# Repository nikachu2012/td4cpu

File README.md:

# TD4 CPU
書籍「CPUの創りかた」にあるTD4 CPUの回路を、ユニバーサル基板で作るのがめんどくさかったので基板にしたものです。
製作の際は書籍を購入することをお勧めします。

*完成させた基板のサンプル*

## フォルダ解説
### `schematic`
回路図と基板のKiCadデータが入っています。バージョンは8.0です。
なんかのフットプリントをライブラリで入れてた気がしますがなくても読めるっぽいです。

### `schematic_pdf`
回路図のpdfファイルが入っています。

### `rom_emulator`
ArduinoなどのマイコンでROMを作るためのプログラムが入っています。  
Arduino UNO系と、Raspberry Pi Pico(MicroPython)があります。

#### Arduino UNO系
Arduino UNO R4 WiFiで動作確認しています。  
ポートレジスタの操作ではなく`digitalWrite`を使っているのでMinimaやR3でも動くと思います。

以下のように接続してください。

| Arduino側 | TD4 CPU側     |
| --------- | ------------- |
| VIN       | +5V           |
| GND       | GND           |
| D11       | Address bus 3 |
| D10       | Address bus 2 |
| D9        | Address bus 1 |
| D8        | Address bus 0 |
| D7        | Data bus 7    |
| D6        | Data bus 6    |
| D5        | Data bus 5    |
| D4        | Data bus 4    |
| D3        | Data bus 3    |
| D2        | Data bus 2    |
| D1        | Data bus 1    |
| D0        | Data bus 0    |

#### Raspberry Pi Pico
Raspberry Pi Pico無印で動作確認済みです。
ファイル名を`main.py`に変更して送信すれば動作すると思います。

以下のように接続してください。

| Raspberry Pi Pico側 | TD4 CPU側     |
| ------------------- | ------------- |
| 39 VSYS             | +5V           |
| 38 GND              | GND           |
| 4  GP2              | Address bus 3 |
| 5  GP3              | Address bus 2 |
| 6  GP4              | Address bus 1 |
| 7  GP5              | Address bus 0 |
| 9  GP6              | Data bus 7    |
| 10 GP7              | Data bus 6    |
| 11 GP8              | Data bus 5    |
| 12 GP9              | Data bus 4    |
| 13 GP10             | Data bus 3    |
| 14 GP11             | Data bus 2    |
| 15 GP12             | Data bus 1    |
| 16 GP13             | Data bus 0    |

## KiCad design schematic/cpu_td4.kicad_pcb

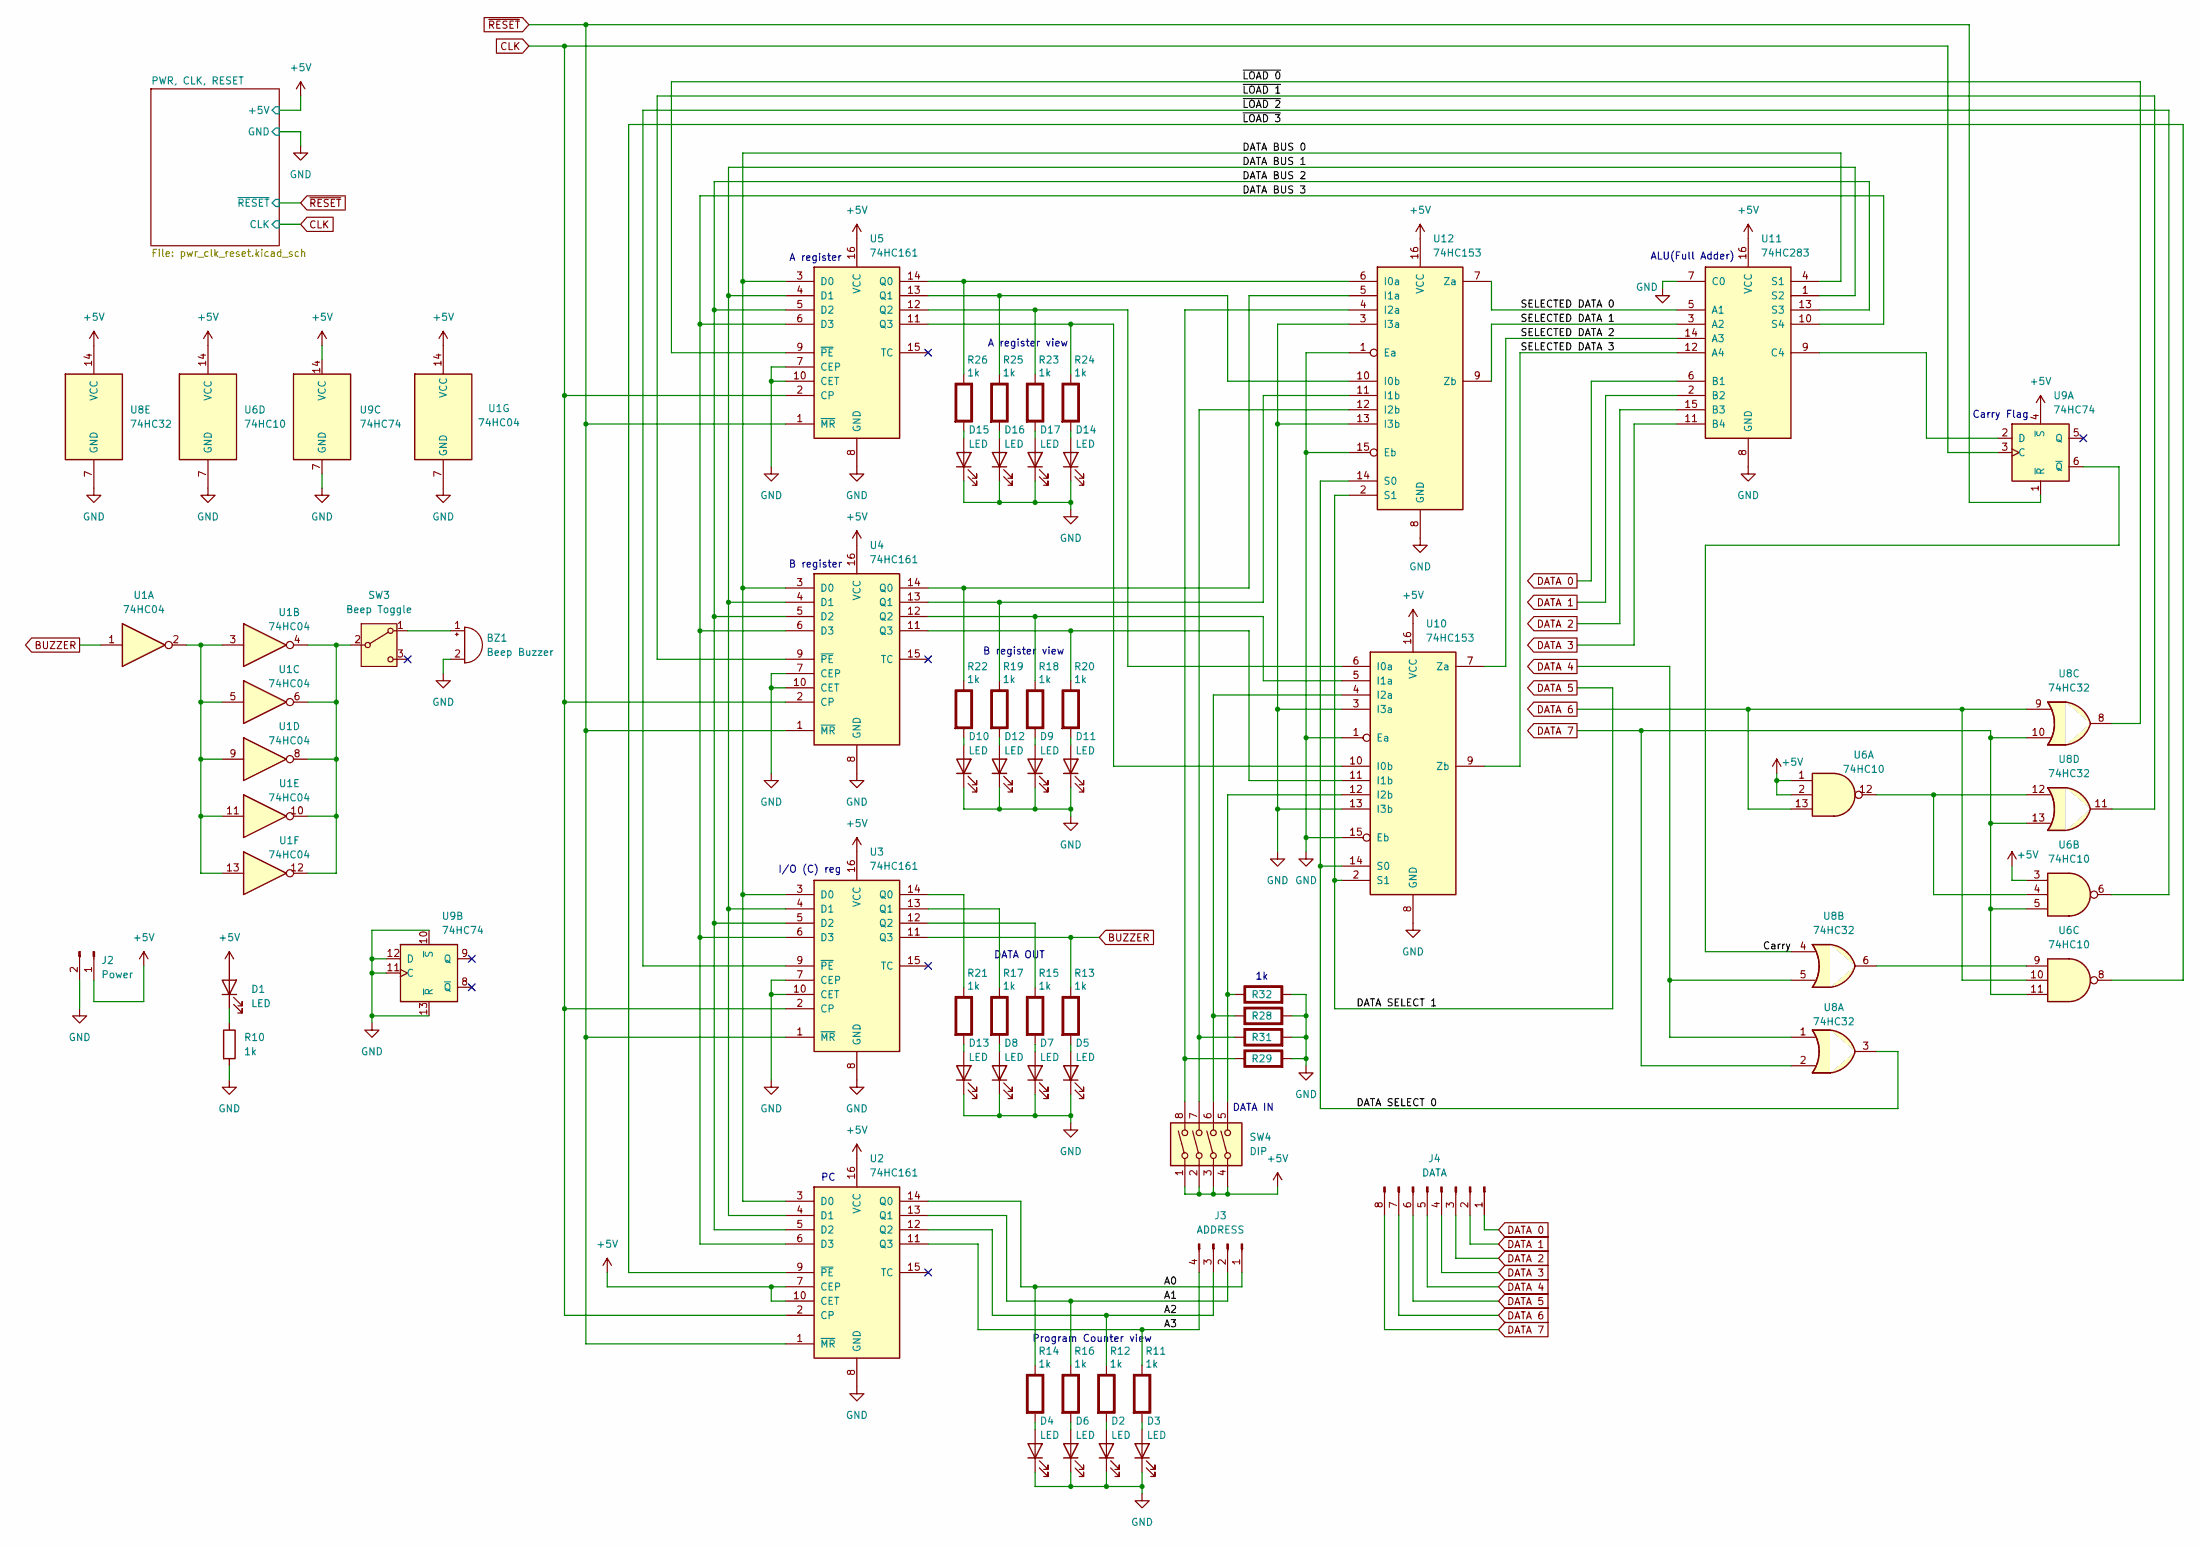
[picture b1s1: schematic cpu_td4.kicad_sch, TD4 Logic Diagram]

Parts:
BZ1: Beep Buzzer; Buzzer_12x9.5RM7.6
D1, D2, D3, D4, D5, D6, D7, D8, D9, D10, D11, D12, D13, D14, D15, D16, D17: LED; LED_D3.0mm
J2: Power; PinHeader_1x02_P2.54mm_Vertical
J3: ADDRESS; PinHeader_1x04_P2.54mm_Vertical
J4: DATA; PinHeader_1x08_P2.54mm_Vertical
R10: 1k; R_Axial_DIN0207_L6.3mm_D2.5mm_P7.62mm_Horizontal
R11, R12, R13, R14, R15, R16, R17, R18, R19, R20, R21, R22, R23, R24, R25, R26, R28, R29, R31, R32: 1k; R_Axial_DIN0207_L6.3mm_D2.5mm_P7.62mm_Horizontal; Rating W
SW3: Beep Toggle; SS12D00G3
SW4: DIP; SW_DIP_SPSTx04_Slide_9.78x12.34mm_W7.62mm_P2.54mm
U1: 74HC04; DIP-14_W7.62mm_Socket
U2, U3, U4, U5: 74HC161; DIP-16_W7.62mm_Socket
U6: 74HC10; DIP-14_W7.62mm_Socket
U8: 74HC32; DIP-14_W7.62mm_Socket
U9: 74HC74; DIP-14_W7.62mm_Socket
U10, U12: 74HC153; DIP-16_W7.62mm_Socket
U11: 74HC283; DIP-16_W7.62mm_Socket

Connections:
+5V: D1.2 (A), J2.1, SW4.1, SW4.2, SW4.3, SW4.4, U1.14 (VCC), U2.7 (CEP), U2.10 (CET), U2.16 (VCC), U3.16 (VCC), U4.16 (VCC), U5.16 (VCC), U6.1, U6.2, U6.3, U6.14 (VCC), U8.14 (VCC), U9.4 (~S), U9.14 (VCC), U10.16 (VCC), U11.16 (VCC), U12.16 (VCC); also elsewhere on the board
/A0: J3.1, R14.1 (+), U2.14 (Q0)
/A1: J3.2, R16.1 (+), U2.13 (Q1)
/A2: J3.3, R12.1 (+), U2.12 (Q2)
/A3: J3.4, R11.1 (+), U2.11 (Q3)
/Carry: U8.4, U9.6 (~Q)
/DATA BUS 0: U2.3 (D0), U3.3 (D0), U4.3 (D0), U5.3 (D0), U11.4 (S1)
/DATA BUS 1: U2.4 (D1), U3.4 (D1), U4.4 (D1), U5.4 (D1), U11.1 (S2)
/DATA BUS 2: U2.5 (D2), U3.5 (D2), U4.5 (D2), U5.5 (D2), U11.13 (S3)
/DATA BUS 3: U2.6 (D3), U3.6 (D3), U4.6 (D3), U5.6 (D3), U11.10 (S4)
/DATA SELECT 0: U8.3, U10.14 (S0), U12.14 (S0)
/SELECTED DATA 0: U11.5 (A1), U12.7 (Za)
/SELECTED DATA 1: U11.3 (A2), U12.9 (Zb)
/SELECTED DATA 2: U10.7 (Za), U11.14 (A3)
/SELECTED DATA 3: U10.9 (Zb), U11.12 (A4)
/~LOAD 0: U5.9 (~PE), U8.8
/~LOAD 1: U4.9 (~PE), U8.11
/~LOAD 2: U3.9 (~PE), U6.6
/~LOAD 3: U2.9 (~PE), U6.8
BUZZER: R13.1 (+), U1.1, U3.11 (Q3)
CLK: U2.2 (CP), U3.2 (CP), U4.2 (CP), U5.2 (CP), U9.3 (C); also elsewhere on the board
DATA 0: J4.1, U11.6 (B1)
DATA 1: J4.2, U11.2 (B2)
DATA 2: J4.3, U11.15 (B3)
DATA 3: J4.4, U11.11 (B4)
DATA 4: J4.5, U8.1, U8.5
DATA 5: J4.6, U10.2 (S1), U12.2 (S1)
DATA 6: J4.7, U6.10, U6.13, U8.9
DATA 7: J4.8, U6.5, U6.11, U8.2, U8.10, U8.13
GND: BZ1.2 (-), D2.1 (K), D3.1 (K), D4.1 (K), D5.1 (K), D6.1 (K), D7.1 (K), D8.1 (K), D9.1 (K), D10.1 (K), D11.1 (K), D12.1 (K), D13.1 (K), D14.1 (K), D15.1 (K), D16.1 (K), D17.1 (K), J2.2, R10.2, R28.2 (-), R29.2 (-), R31.2 (-), R32.2 (-), U1.7 (GND), U2.8 (GND), U3.7 (CEP), U3.8 (GND), U3.10 (CET), U4.7 (CEP), U4.8 (GND), U4.10 (CET), U5.7 (CEP), U5.8 (GND), U5.10 (CET), U6.7 (GND), U8.7 (GND), U9.7 (GND), U9.10 (~S), U9.11 (C), U9.12 (D), U9.13 (~R), U10.1 (Ea), U10.3 (I3a), U10.8 (GND), U10.13 (I3b), U10.15 (Eb), U11.7 (C0), U11.8 (GND), U12.1 (Ea), U12.3 (I3a), U12.8 (GND), U12.13 (I3b), U12.15 (Eb); also elsewhere on the board
unnamed: BZ1.1 (+), SW3.1 (A)
unnamed: D1.1 (K), R10.1
unnamed: D2.2 (A), R12.2 (-)
unnamed: D3.2 (A), R11.2 (-)
unnamed: D4.2 (A), R14.2 (-)
unnamed: D5.2 (A), R13.2 (-)
unnamed: D6.2 (A), R16.2 (-)
unnamed: D7.2 (A), R15.2 (-)
unnamed: D8.2 (A), R17.2 (-)
unnamed: D9.2 (A), R18.2 (-)
unnamed: D10.2 (A), R22.2 (-)
unnamed: D11.2 (A), R20.2 (-)
unnamed: D12.2 (A), R19.2 (-)
unnamed: D13.2 (A), R21.2 (-)
unnamed: D14.2 (A), R24.2 (-)
unnamed: D15.2 (A), R26.2 (-)
unnamed: D16.2 (A), R25.2 (-)
unnamed: D17.2 (A), R23.2 (-)
unnamed: R15.1 (+), U3.12 (Q2)
unnamed: R17.1 (+), U3.13 (Q1)
unnamed: R18.1 (+), U4.12 (Q2), U10.5 (I1a)
unnamed: R19.1 (+), U4.13 (Q1), U12.11 (I1b)
unnamed: R20.1 (+), U4.11 (Q3), U10.11 (I1b)
unnamed: R21.1 (+), U3.14 (Q0)
unnamed: R22.1 (+), U4.14 (Q0), U12.5 (I1a)
unnamed: R23.1 (+), U5.12 (Q2), U10.6 (I0a)
unnamed: R24.1 (+), U5.11 (Q3), U10.10 (I0b)
unnamed: R25.1 (+), U5.13 (Q1), U12.10 (I0b)
unnamed: R26.1 (+), U5.14 (Q0), U12.6 (I0a)
unnamed: R28.1 (+), SW4.6, U10.4 (I2a)
unnamed: R29.1 (+), SW4.8, U12.4 (I2a)
unnamed: R31.1 (+), SW4.7, U12.12 (I2b)
unnamed: R32.1 (+), SW4.5, U10.12 (I2b)
unnamed: SW3.2 (B), U1.4, U1.6, U1.8, U1.10, U1.12
unnamed: U1.2, U1.3, U1.5, U1.9, U1.11, U1.13
unnamed: U6.9, U8.6
unnamed: U6.4, U6.12, U8.12
unnamed: U9.2 (D), U11.9 (C4)
~RESET: U2.1 (~MR), U3.1 (~MR), U4.1 (~MR), U5.1 (~MR), U9.1 (~R); also elsewhere on the board

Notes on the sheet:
ALU(Full Adder)
A register view
DATA OUT
B register
I/O (C) reg
Program Counter view
B register view
A register
DATA IN
Carry Flag

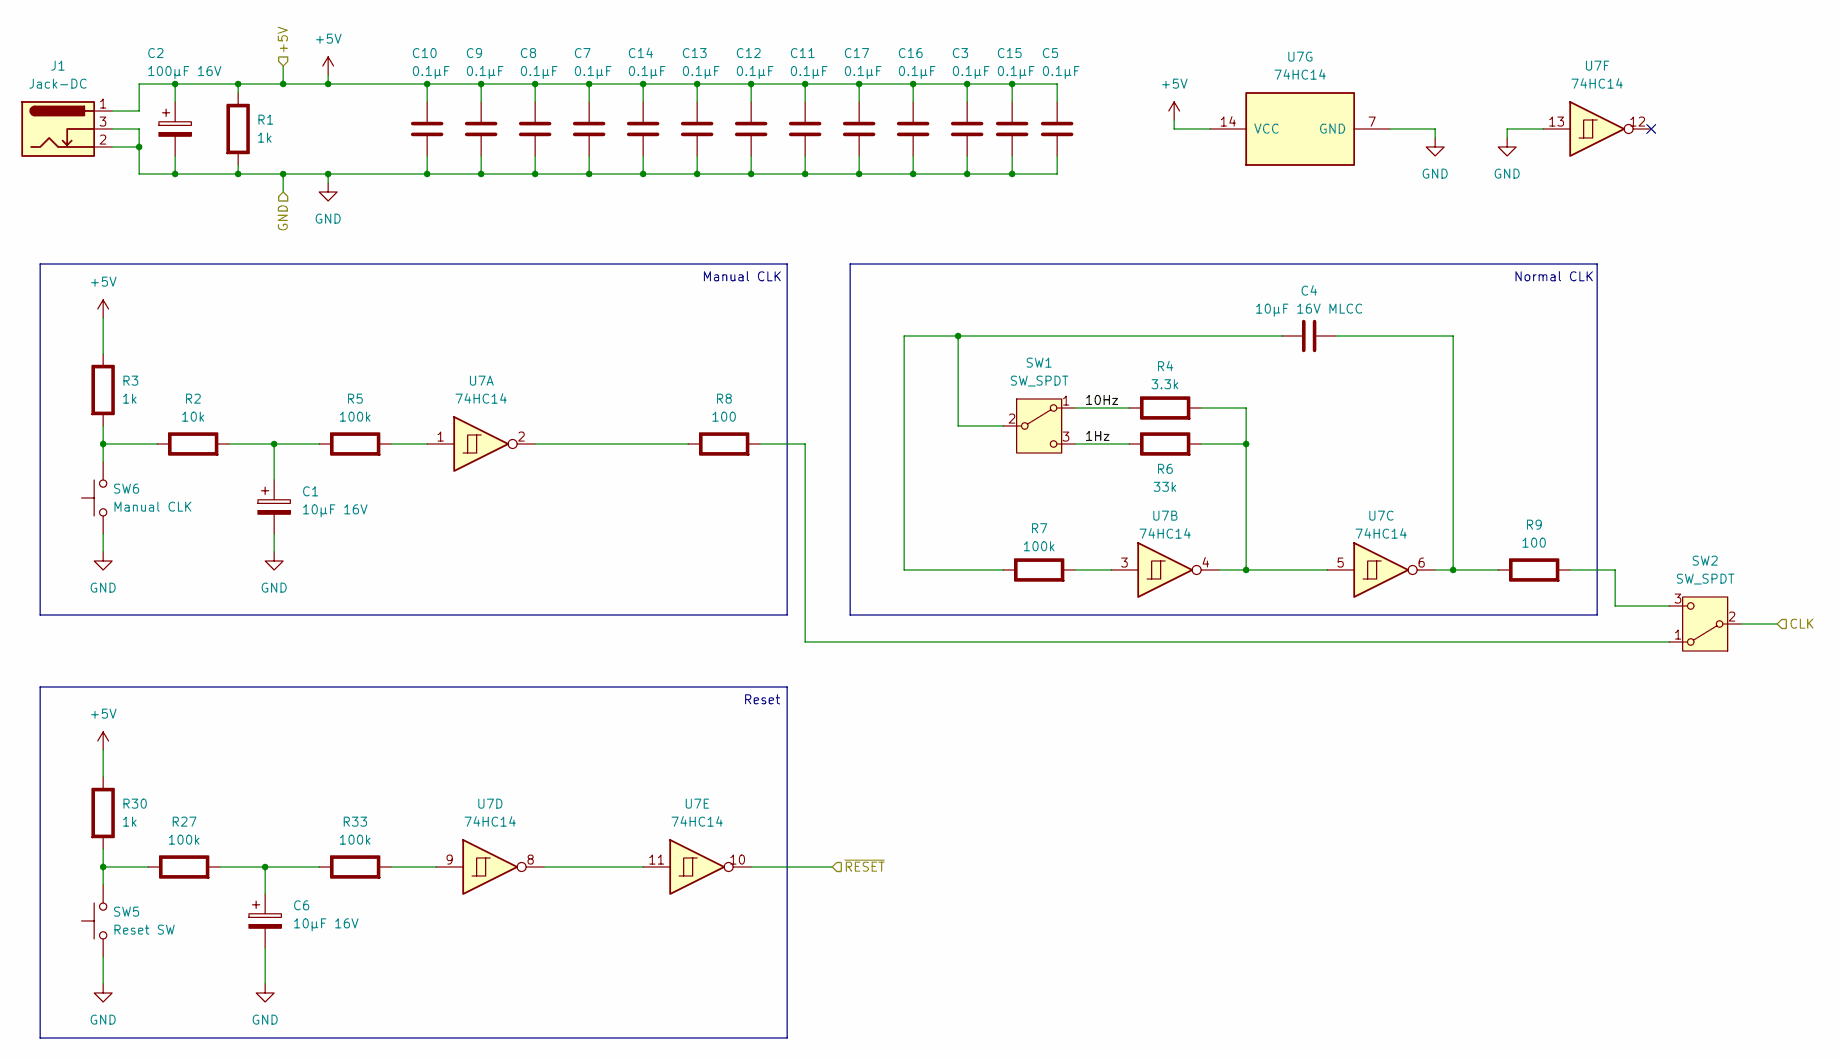
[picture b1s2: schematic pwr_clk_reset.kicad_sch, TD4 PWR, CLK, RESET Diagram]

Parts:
C1, C6: 10μF 16V; CP_Radial_D4.0mm_P1.50mm
C2: 100μF 16V; CP_Radial_D6.3mm_P2.50mm
C3, C5, C7, C8, C9, C10, C11, C12, C13, C14, C15, C16, C17: 0.1μF; C_Disc_D5.0mm_W2.5mm_P2.50mm
C4: 10μF 16V MLCC; C_Disc_D6.0mm_W2.5mm_P5.00mm
J1: Jack-DC; BarrelJack_GCT_DCJ200-10-A_Horizontal
R1, R3, R30: 1k; R_Axial_DIN0207_L6.3mm_D2.5mm_P7.62mm_Horizontal; Rating W
R2: 10k; R_Axial_DIN0207_L6.3mm_D2.5mm_P7.62mm_Horizontal; Rating W
R4: 3.3k; R_Axial_DIN0207_L6.3mm_D2.5mm_P7.62mm_Horizontal; Rating W
R5, R7, R27, R33: 100k; R_Axial_DIN0207_L6.3mm_D2.5mm_P7.62mm_Horizontal; Rating W
R6: 33k; R_Axial_DIN0207_L6.3mm_D2.5mm_P7.62mm_Horizontal; Rating W
R8, R9: 100; R_Axial_DIN0207_L6.3mm_D2.5mm_P7.62mm_Horizontal; Rating W
SW1, SW2: SW_SPDT; SS12D00G3
SW5: Reset SW; SW_PUSH-12mm_Wuerth-430476085716
SW6: Manual CLK; SW_PUSH-12mm_Wuerth-430476085716
U7: 74HC14; DIP-14_W7.62mm_Socket

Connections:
+5V: C2.1, C3.1, C5.1, C7.1, C8.1, C9.1, C10.1, C11.1, C12.1, C13.1, C14.1, C15.1, C16.1, C17.1, J1.1, R1.1 (+), R3.1 (+), R30.1 (+), U7.14 (VCC); also elsewhere on the board
/PWR, CLK, RESET/1Hz: R6.1 (+), SW1.3 (C)
/PWR, CLK, RESET/10Hz: R4.1 (+), SW1.1 (A)
CLK: SW2.2 (B); also elsewhere on the board
GND: C1.2, C2.2, C3.2, C5.2, C6.2, C7.2, C8.2, C9.2, C10.2, C11.2, C12.2, C13.2, C14.2, C15.2, C16.2, C17.2, J1.2, J1.3, R1.2 (-), SW5.1, SW6.1, U7.7 (GND), U7.13; also elsewhere on the board
unnamed: R2.1 (+), R3.2 (-), SW6.2
unnamed: C1.1, R2.2 (-), R5.1 (+)
unnamed: R4.2 (-), R6.2 (-), U7.4, U7.5
unnamed: R5.2 (-), U7.1
unnamed: C4.1, R7.1 (+), SW1.2 (B)
unnamed: R7.2 (-), U7.3
unnamed: R8.1 (+), U7.2
unnamed: R8.2 (-), SW2.1 (A)
unnamed: C4.2, R9.1 (+), U7.6
unnamed: R9.2 (-), SW2.3 (C)
unnamed: R27.1 (+), R30.2 (-), SW5.2
unnamed: C6.1, R27.2 (-), R33.1 (+)
unnamed: R33.2 (-), U7.9
unnamed: U7.8, U7.11
~RESET: U7.10; also elsewhere on the board

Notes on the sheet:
Manual CLK
Normal CLK
Reset

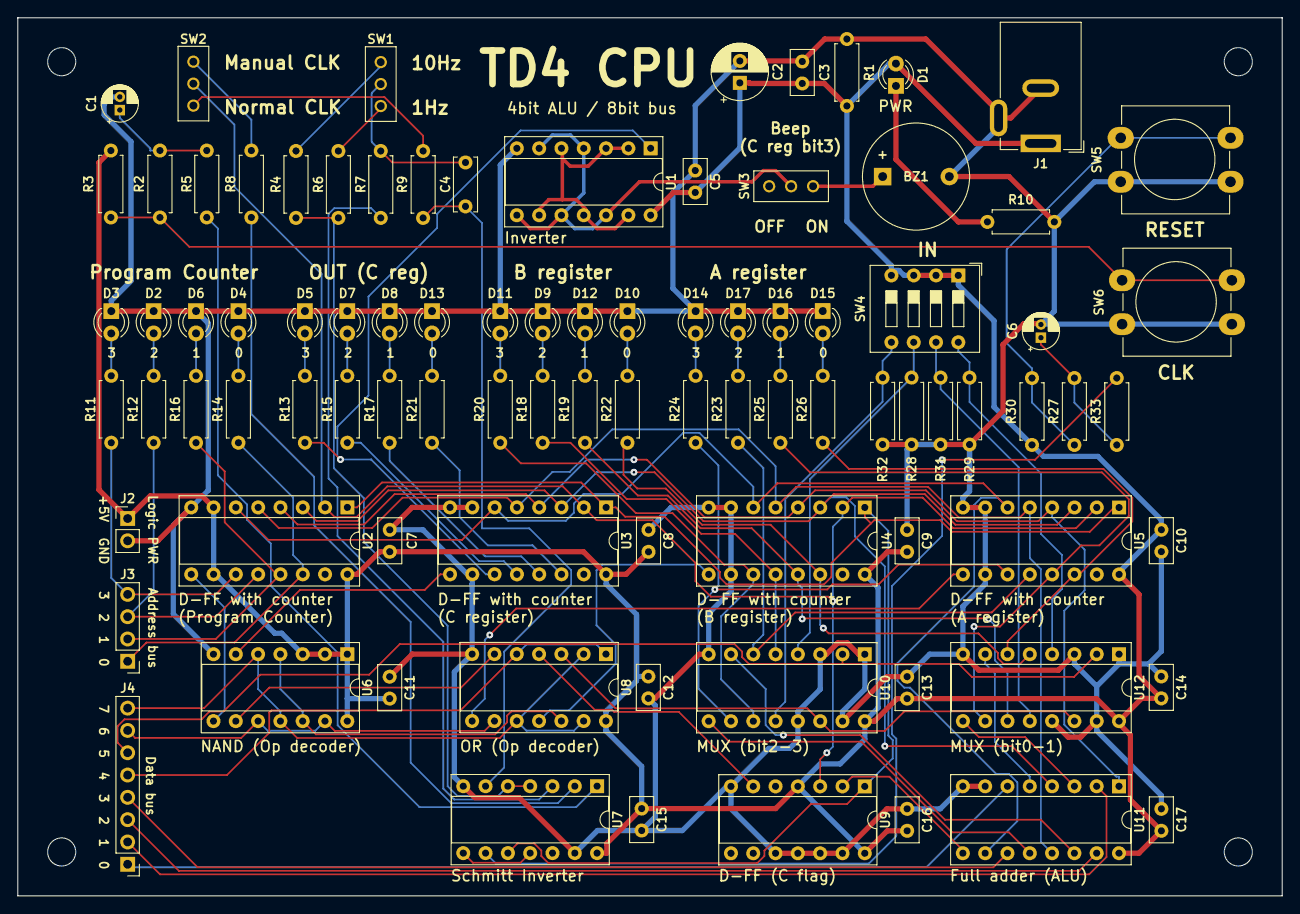
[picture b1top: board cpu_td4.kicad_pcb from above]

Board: 2 copper layers, 144.0 x 100.0 mm, 90 parts (0 on the bottom side), 85 nets.

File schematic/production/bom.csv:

Designator,Footprint,Quantity,Value,LCSC Part #
BZ1,Buzzer_12x9.5RM7.6,1,Beep Buzzer,
"C1, C6",CP_Radial_D4.0mm_P1.50mm,2,10μF 16V,
"C10, C11, C12, C13, C14, C15, C16, C17, C3, C5, C7, C8, C9",C_Disc_D5.0mm_W2.5mm_P2.50mm,13,0.1μF,
C2,CP_Radial_D6.3mm_P2.50mm,1,100μF 16V,
C4,C_Disc_D6.0mm_W2.5mm_P5.00mm,1,10μF 16V MLCC,
"D1, D10, D11, D12, D13, D14, D15, D16, D17, D2, D3, D4, D5, D6, D7, D8, D9",LED_D3.0mm,17,LED,
J1,BarrelJack_GCT_DCJ200-10-A_Horizontal,1,Jack-DC,
J2,PinHeader_1x02_P2.54mm_Vertical,1,Power,
J3,PinHeader_1x04_P2.54mm_Vertical,1,ADDRESS,
J4,PinHeader_1x08_P2.54mm_Vertical,1,DATA,
"R1, R10, R11, R12, R13, R14, R15, R16, R17, R18, R19, R20, R21, R22, R23, R24, R25, R26, R28, R29, R3, R30, R31, R32",R_Axial_DIN0207_L6.3mm_D2.5mm_P7.62mm_Horizontal,24,1k,
R2,R_Axial_DIN0207_L6.3mm_D2.5mm_P7.62mm_Horizontal,1,10k,
"R27, R33, R5, R7",R_Axial_DIN0207_L6.3mm_D2.5mm_P7.62mm_Horizontal,4,100k,
R4,R_Axial_DIN0207_L6.3mm_D2.5mm_P7.62mm_Horizontal,1,3.3k,
R6,R_Axial_DIN0207_L6.3mm_D2.5mm_P7.62mm_Horizontal,1,33k,
"R8, R9",R_Axial_DIN0207_L6.3mm_D2.5mm_P7.62mm_Horizontal,2,100,
"SW1, SW2",SS12D00G3,2,SW_SPDT,
SW3,SS12D00G3,1,Beep Toggle,
SW4,SW_DIP_SPSTx04_Slide_9.78x12.34mm_W7.62mm_P2.54mm,1,DIP,
SW5,SW_PUSH-12mm_Wuerth-430476085716,1,Reset SW,
SW6,SW_PUSH-12mm_Wuerth-430476085716,1,Manual CLK,
U1,DIP-14_W7.62mm_Socket,1,74HC04,
"U10, U12",DIP-16_W7.62mm_Socket,2,74HC153,
U11,DIP-16_W7.62mm_Socket,1,74HC283,
"U2, U3, U4, U5",DIP-16_W7.62mm_Socket,4,74HC161,
U6,DIP-14_W7.62mm_Socket,1,74HC10,
U7,DIP-14_W7.62mm_Socket,1,74HC14,
U8,DIP-14_W7.62mm_Socket,1,74HC32,
U9,DIP-14_W7.62mm_Socket,1,74HC74,

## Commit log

2024-11-02 [init]
2024-11-04 [add] 8bit整数値をROMのデータとして利用できるように変更
2024-11-04 [add] 本の説明書を追加
2024-11-04 [add] PDFのBOMを追加
2024-11-04 ページ数を１削減
2024-11-06 [fix] タイトルの変更とISBNの修正
2024-11-07 [update] 偶数セルに色を付けるように変更
